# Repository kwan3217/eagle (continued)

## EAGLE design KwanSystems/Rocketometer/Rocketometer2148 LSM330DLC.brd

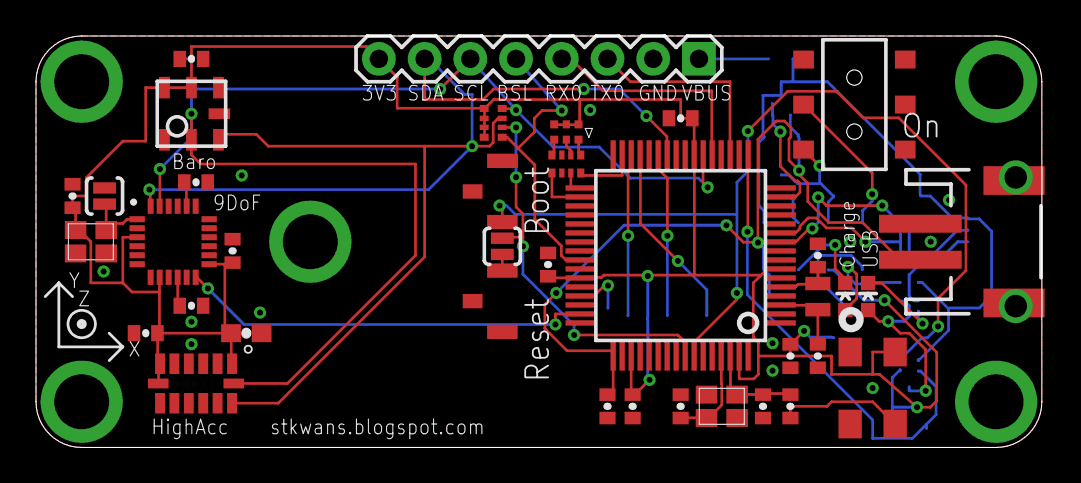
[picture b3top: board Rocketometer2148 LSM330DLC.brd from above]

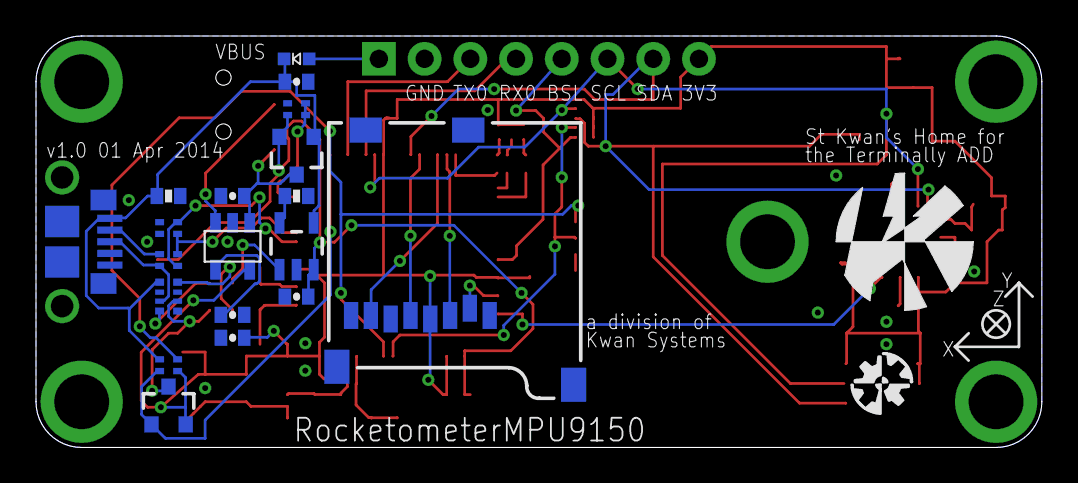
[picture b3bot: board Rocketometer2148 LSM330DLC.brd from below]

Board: 2 copper layers, 55.9 x 22.9 mm, 64 parts (21 on the bottom side), 46 nets.

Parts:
C023: 22pF; CKCM25
C101, C203, C443, C449, C601, C610, C613, C906: 100nF; 0402-CAP
C201, C301, C302: 4.7uF; 0402-CAP
C204, C423, C451, C463: 1uF; 0402-CAP
C403, C405: 22pF; 0402-CAP
C404: 100pF; 0402-CAP
C461, C462: 33pF; 0402-CAP
C620: 2.2nF; 0402-CAP
C901: 10uF; 0603-CAP
D050: BLUE; LED-0603
D301: YELLOW; LED-0603
D302: DCC; SOT-23-3
D401: SMLP36
D402: DIODE_SCHOTTKY; D0603
J001: USB_MICROB_JSTGCT; USB_MICROB_3075
J301: JST 2mm; JST-2-SMD
J401: M07; 1X08
J701: MICROSD-SOCKET; MICROSD-SOCKET-PP
JP1, JP2, JP3, JP4, JP5: STANDOFF
Q050: PMOS; SOT23-3
R011: 100k; 0402-RES
R015: 10k; CRA02
R023: 33; CRA02
R053, R402: 1.5k; CRA04
R301: 10k; 0402-RES
R302: 1M; CRA02
R401: 10k; CRA04
S201: AYZ0202
S457, S458: B3U-1100P
S457A, S457A1: SOLDERJUMPERNO; SJ_2S-NO
U101: BMP180
U201: 5319; SOT-23-5
U301: 73831; SOT23-5
U401: LPC2148; SQFP-S-10X10-64
U601: MPU9150; LLGA24
U902: ADXL375
U$4: AXES
U$5: KWAN_ACC
U$6: OSHW_ACC
Y401: 12MHz; CRYSTAL_SMD_2MM_2_5MM
Y402: 32kiHz; ABS06
Y403: 12MHz; CRYSTAL_SMD_5MM_3_2MM
Y601: 19.2MHz; CRYSTAL_SMD_2MM_2_5MM

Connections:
ACCINT: U401.47, U601.12
BATLVL: R302.3, R302.4, U401.15
BSL: J401.5, R401.1, U401.41
CONN_D+: J001.3, R023.2, R053.7
CONN_D-: J001.2, R023.1
CS0: J701.2, U401.45
EN: S201.5, U201.3
GND: C023.3, C023.4, C101.2, C201.2, C203.2, C204.2, C301.2, C302.2, C403.1, C405.2, C423.2, C443.2, C449.1, C451.2, C461.1, C462.1, C463.2, C601.1, C610.2, C613.1, C620.1, C901.2, C906.2, J001.5, J001.P$1, J001.P$2, J001.P$3, J001.P$4, J001.P$8, J001.P$10, J301.1, J401.2, J701.6, J701.CD2, J701.GND1, J701.GND3, JP1.P$1, JP2.P$1, JP3.P$1, JP4.P$1, JP5.P$1, R011.1, R053.1, R301.1, R302.1, S201.4, S457.P$2, S457.P$3, S457A1.2, S458.P$1, S458.P$3, U101.7, U201.2, U301.2, U401.6, U401.18, U401.25, U401.42, U401.50, U401.59, U601.9, U601.11, U601.15, U601.17, U601.18, U902.2, U902.4, U902.5, U902.12, Y401.2, Y401.4, Y403.2, Y601.1, Y601.2
MISO0: J701.7, U401.29
MOSI0: J701.3, U401.30
unnamed: C620.2, U601.20
unnamed: R301.2, U301.5
unnamed: D301.A, R053.4
unnamed: D301.C, U301.1
unnamed: C404.2, Y403.3
unnamed: D050.A, Q050.3, R053.2
unnamed: D050.C, R053.8
unnamed: D402.A, J401.1
unnamed: S457.P$1, S457A.2
unnamed: C610.1, U601.10
unnamed: C203.1, U201.4
OSC_9DOF: S457A1.1, U601.1, Y601.3
PWMB: R402.8, U401.31
PWMG: R402.5, U401.34
PWMR: R402.7, U401.33
QWMB: D401.1, R402.1
QWMG: D401.5, R402.4
QWMR: D401.3, R402.2
RESET: R401.2, S457A.1, U401.57
RTXC1: C403.2, U401.3, Y402.2
RTXC2: C405.1, U401.5, Y402.1
RX0: J401.4, U401.21
SCK0: J701.5, U401.27
SCL0: J401.6, R401.4, U101.5, U401.22, U601.23, U902.14
SDA0: J401.7, R401.3, U101.6, U401.26, U601.24, U902.13
TX0: J401.3, U401.19
USBD+: C023.2, R023.3, U401.10
USBD-: C023.1, R023.4, U401.11
USB_ON: R015.2, S458.P$2, U401.58
USB_SOFTCONNECT: Q050.1, R015.4, U401.17
VBUS: C302.1, D302.1, D402.C, J001.1, R011.2, R015.3, R053.5, U301.4
VCC: C101.1, C201.1, C423.1, C443.1, C451.1, C463.1, C601.2, C613.2, C901.1, C906.1, D401.2, D401.4, D401.6, J401.8, J701.4, Q050.2, R015.1, R401.5, R401.6, R401.7, R401.8, U101.2, U101.3, U201.5, U401.7, U401.23, U401.43, U401.51, U401.63, U601.3, U601.8, U601.13, U902.1, U902.6, U902.7, Y403.4, Y601.4
VIN: C204.1, D302.3, S201.6, U201.1
VLIPO: C301.1, C449.2, D302.2, J301.2, R302.2, U301.3, U401.49
XTAL1: C404.1, C462.2, U401.62, Y401.1
XTAL2: C461.2, U401.61, Y401.3

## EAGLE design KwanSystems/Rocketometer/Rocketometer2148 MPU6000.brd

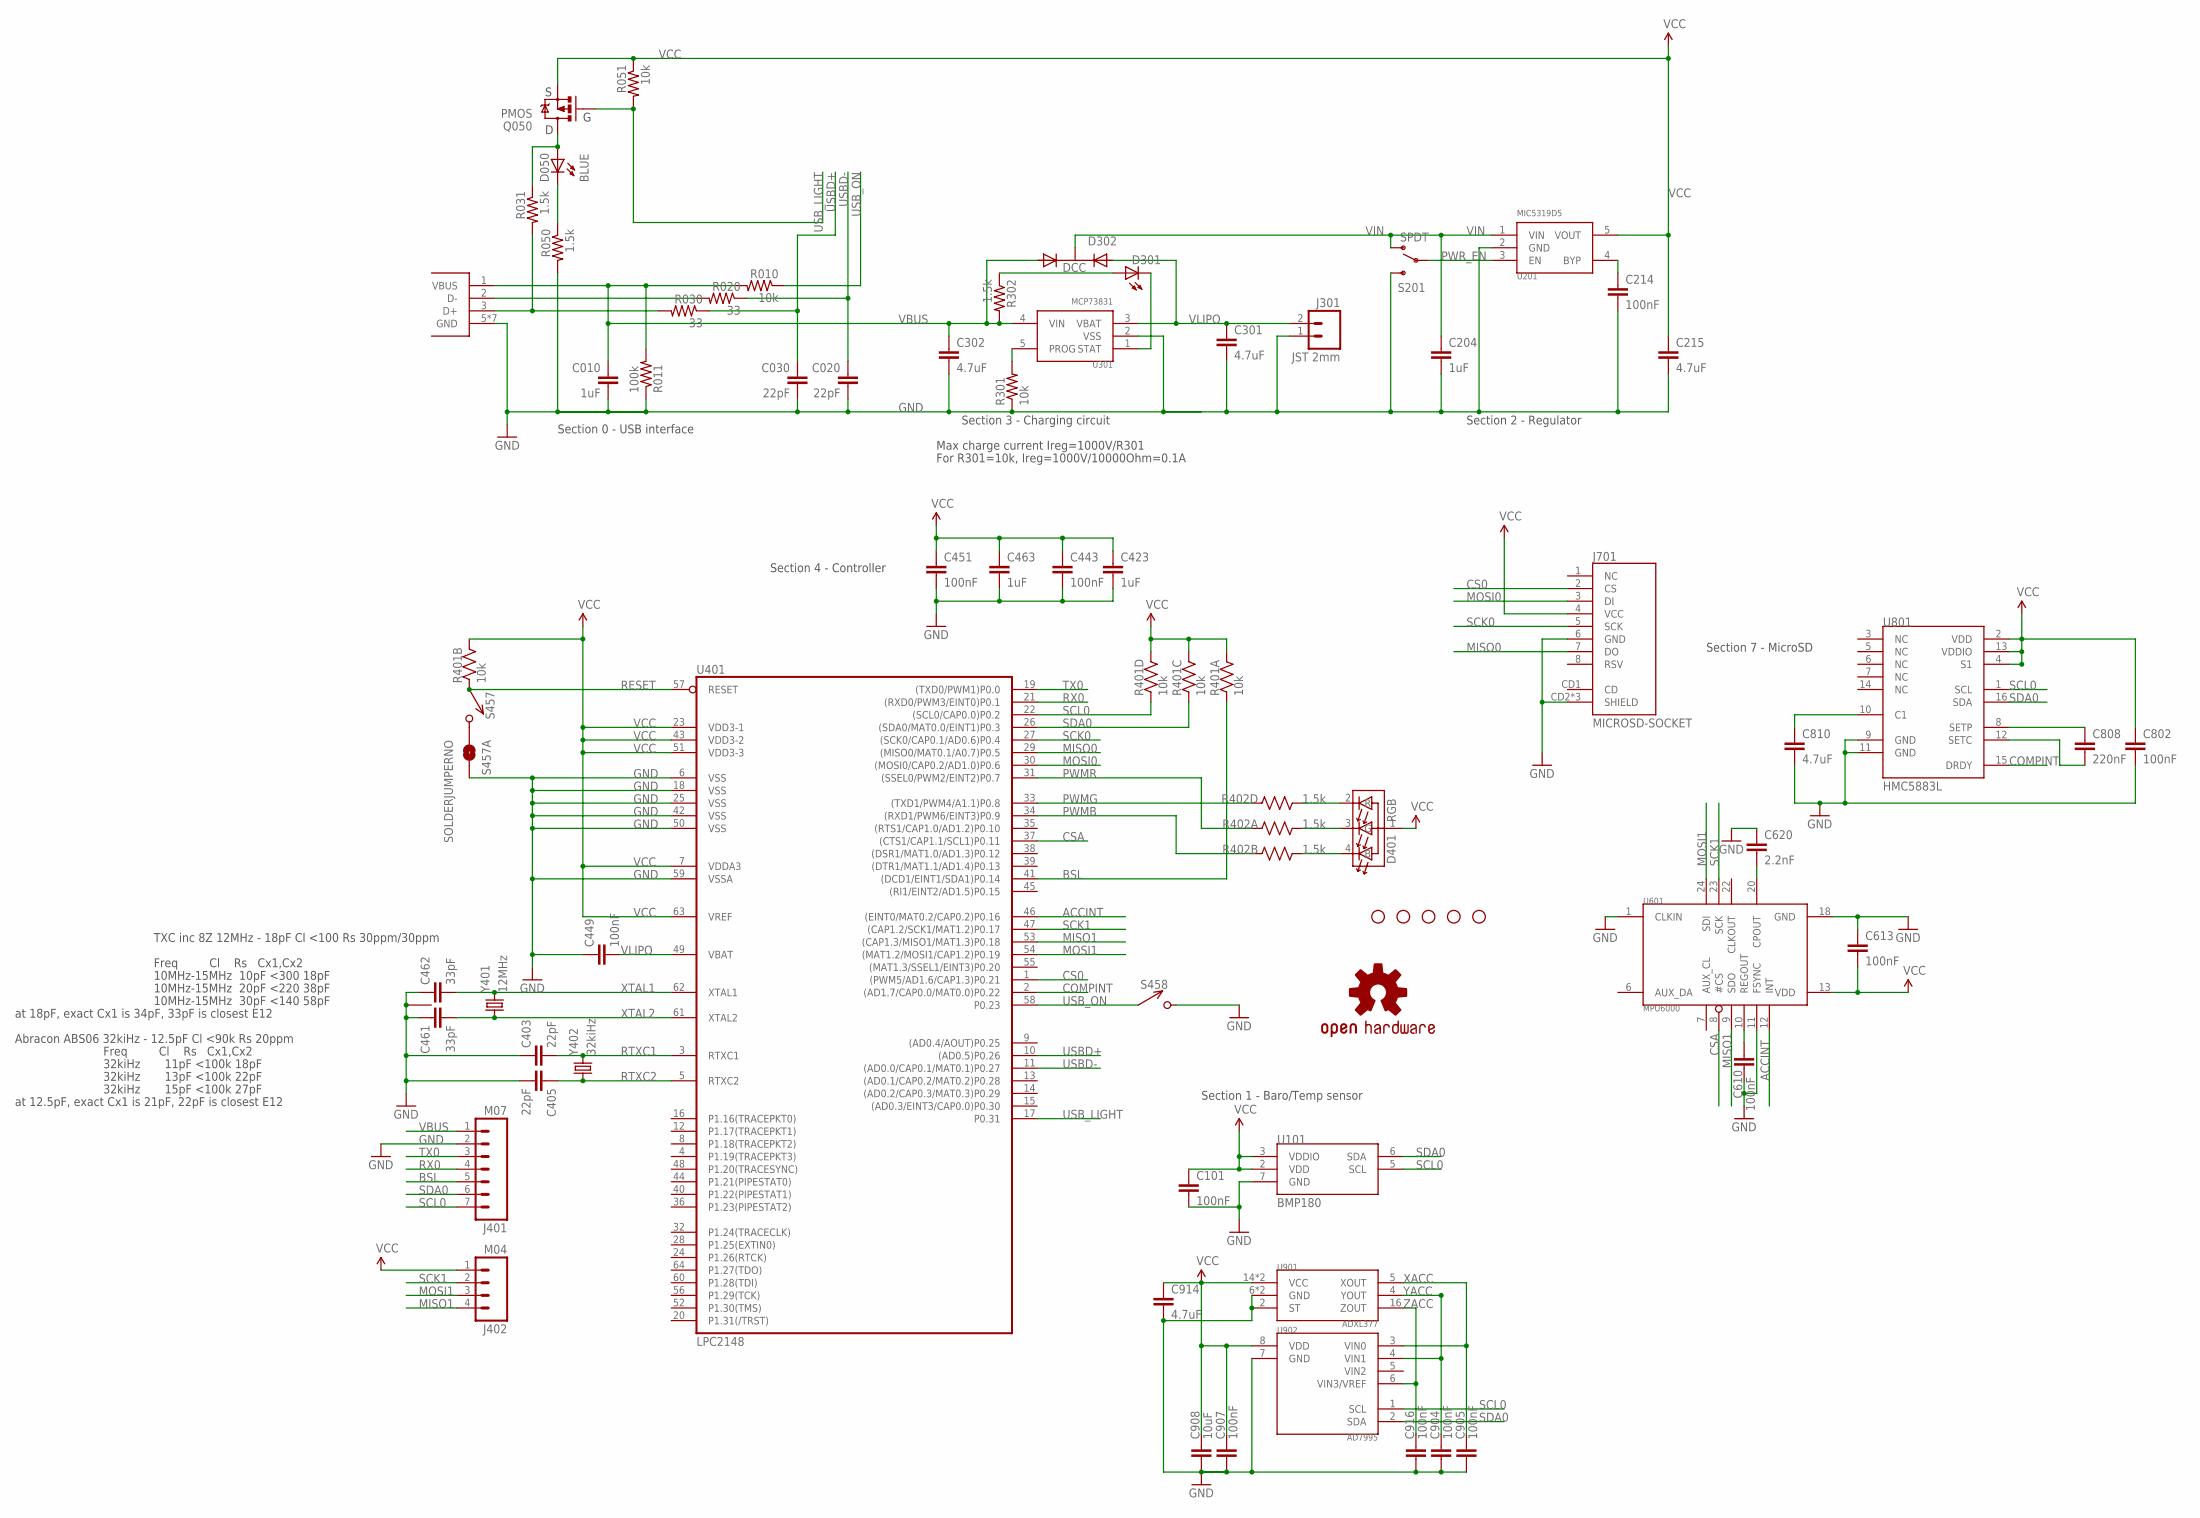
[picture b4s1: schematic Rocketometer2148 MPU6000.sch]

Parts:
C010, C204, C423, C463: 1uF; 0402-CAP; DIGIKEY 445-1415-1-ND
C020, C030, C403, C405: 22pF; 0402-CAP; DIGIKEY 445-5363-1-ND
C101, C214, C443, C449, C451, C610, C613, C802, C904, C905, C907, C916: 100nF; 0402-CAP; DIGIKEY 445-1268-1-ND
C215, C301, C302, C810, C914: 4.7uF; 0402-CAP; DIGIKEY 445-7395-1-ND
C461, C462: 33pF; 0402-CAP; DIGIKEY 445-1241-1-ND
C620: 2.2nF; 0402-CAP; DIGIKEY 445-1257-1-ND
C808: 220nF; 0402-CAP; DIGIKEY 445-4972-1-ND
C908: 10uF; 0603-CAP; DIGIKEY 445-7486-1-ND
D050: BLUE; LED-0603; DIGIKEY 350-2037-1-ND
D301: YELLOW; LED-0603; DIGIKEY 754-1124-1-ND
D302: DCC; SOT-23-3; DIGIKEY 568-6500-1-ND
D401: RGB; HSMF-C118; DIGIKEY 516-1778-1-ND
J001: USB_MICROB_JST; UB-MC5BR3-SD204-4S; DIGIKEY 455-2562-1-ND
J301: JST 2mm; JST-2-SMD; DIGIKEY 455-1749-1-ND
J401: M07; 1X07; DIGIKEY $NOPART
J402: M04; 1X04; DIGIKEY $NOPART
J701: MICROSD-SOCKET; MICROSD-SOCKET-PP; DIGIKEY 101-00581-59-1-ND
JP1, JP2, JP3, JP4, JP5: STAND-OFFTIGHT; STAND-OFF-TIGHT; DIGIKEY $NOPART
Q050: PMOS; SOT23-3; DIGIKEY NTR1P02T1GOSCT-ND
R010, R051, R301: 10k; 0402-RES; DIGIKEY P10.0KLCT-ND
R011: 100k; 0402-RES; DIGIKEY P100KLCT-ND
R020, R030: 33; 0402-RES; DIGIKEY P33.0LCT-ND
R031, R050, R302: 1.5k; 0402-RES; DIGIKEY P1.50KLCT-ND
R401: 10k; CRA04; DIGIKEY CRA4S810KCT-ND
R402: 1.5k; CRA04; DIGIKEY CRA4S81.5KCT-ND
S201: SPDT; AYZ0202; DIGIKEY 401-2013-1-ND
S457, S458: B3U-1000P; DIGIKEY SW1020CT-ND
S457A: SOLDERJUMPERNO; SJ_2S-NO; DIGIKEY $NOPART
U101: BMP180; DIGIKEY 828-1027-1-ND
U201: MIC5319D5; SOT-23-5; DIGIKEY 576-1910-1-ND
U301: MCP73831; SOT-23-5; DIGIKEY MCP73831T-2ACI/OTCT-ND
U401: LPC2148; SQFP-S-10X10-64; DIGIKEY 568-1765-ND
U601: MPU6000; MPU60X0; DIGIKEY $NOPART
U801: HMC5883L; 16LPCC; DIGIKEY 342-1082-1-ND
U901: ADXL377; DIGIKEY ADXL377BCPZ-RL7CT-ND
U902: AD7995; SOT-23-8; DIGIKEY AD7995YRJZ-1500RL7CT-ND
U$2: OSHW-LOGOS; OSHW-LOGO-S; DIGIKEY $NOPART
Y401: 12MHz; CRYSTAL_SMD_2MM_2_5MM; DIGIKEY 887-1487-1-ND
Y402: 32kiHz; ABS06; DIGIKEY 535-10104-1-ND

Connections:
ACCINT: U401.46 ((EINT0/MAT0.2/CAP0.2)P0.16), U601.12 (INT)
BSL: J401.5, R401.1, U401.41 ((DCD1/EINT1/SDA1)P0.14)
COMPINT: U401.2 ((AD1.7/CAP0.0/MAT0.0)P0.22), U801.15 (DRDY)
CONN_D+: J001.3 (D+), R030.2, R031.2
CONN_D-: J001.2 (D-), R020.2
CS0: J701.2 (CS), U401.1 ((PWM5/AD1.6/CAP1.3)P0.21)
CSA: U401.37 ((CTS1/CAP1.1/SCL1)P0.11), U601.8 (#CS)
GND: C010.2, C020.2, C030.2, C101.2, C204.2, C214.2, C215.2, C301.2, C302.2, C403.1, C405.2, C423.2, C443.2, C449.1, C451.2, C461.1, C462.1, C463.2, C610.2, C613.1, C620.1, C802.2, C810.2, C904.2, C905.2, C907.2, C908.2, C914.2, C916.2, J001.5 (GND), J001.P$6 (GND), J001.P$7 (GND), J001.P$8 (GND), J001.P$9 (GND), J001.P$10 (GND), J001.P$11 (GND), J301.1, J401.2, J701.6 (GND), J701.CD2 (SHIELD), J701.GND1 (SHIELD), J701.GND3 (SHIELD), R011.1, R050.2, R301.1, S201.3 (S), S457A.2, S458.P$2 (2), U101.7 (GND), U201.2 (GND), U301.2 (VSS), U401.6 (VSS), U401.18 (VSS), U401.25 (VSS), U401.42 (VSS), U401.50 (VSS), U401.59 (VSSA), U601.1 (CLKIN), U601.11 (FSYNC), U601.18 (GND), U801.9 (GND), U801.11 (GND), U901.2 (ST), U901.6 (GND), U901.7 (GND), U902.7 (GND), Y401.2 (1), Y401.4 (1)
MISO0: J701.7 (DO), U401.29 ((MISO0/MAT0.1/A0.7)P0.5)
MISO1: J402.4, U401.53 ((CAP1.3/MISO1/MAT1.3)P0.18), U601.9 (SDO)
MOSI0: J701.3 (DI), U401.30 ((MOSI0/CAP0.2/AD1.0)P0.6)
MOSI1: J402.3, U401.54 ((MAT1.2/MOSI1/CAP1.2)P0.19), U601.24 (SDI)
unnamed: C620.2, U601.20 (CPOUT)
unnamed: R301.2, U301.5 (PROG)
unnamed: D401.4 (B), R402.2 (1)
unnamed: D301.C, U301.1 (STAT)
unnamed: D301.A, R302.1
unnamed: D050.A, Q050.3 (D), R031.1
unnamed: D050.C, R050.1
unnamed: S457.P$2 (2), S457A.1
unnamed: D401.2 (R), R402.4 (1)
unnamed: D401.3 (G), R402.1
unnamed: C610.1, U601.10 (REGOUT)
unnamed: C808.1, U801.8 (SETP)
unnamed: C808.2, U801.12 (SETC)
unnamed: C810.1, U801.10 (C1)
unnamed: C214.1, U201.4 (BYP)
PWMB: R402.7 (2), U401.34 ((RXD1/PWM6/EINT3)P0.9)
PWMG: R402.5 (2), U401.33 ((TXD1/PWM4/A1.1)P0.8)
PWMR: R402.8 (2), U401.31 ((SSEL0/PWM2/EINT2)P0.7)
PWR_EN: S201.2, U201.3 (EN)
RESET: R401.2 (1), S457.P$1 (1), U401.57 (RESET)
RTXC1: C403.2, U401.3 (RTXC1), Y402.2
RTXC2: C405.1, U401.5 (RTXC2), Y402.1
RX0: J401.4, U401.21 ((RXD0/PWM3/EINT0)P0.1)
SCK0: J701.5 (SCK), U401.27 ((SCK0/CAP0.1/AD0.6)P0.4)
SCK1: J402.2, U401.47 ((CAP1.2/SCK1/MAT1.2)P0.17), U601.23 (SCK)
SCL0: J401.7, R401.4 (1), U101.5 (SCL), U401.22 ((SCL0/CAP0.0)P0.2), U801.1 (SCL), U902.1 (SCL)
SDA0: J401.6, R401.3 (1), U101.6 (SDA), U401.26 ((SDA0/MAT0.0/EINT1)P0.3), U801.16 (SDA), U902.2 (SDA)
TX0: J401.3, U401.19 ((TXD0/PWM1)P0.0)
USBD+: C030.1, R030.1, U401.10 ((AD0.5)P0.26)
USBD-: C020.1, R020.1, U401.11 ((AD0.0/CAP0.1/MAT0.1)P0.27)
USB_LIGHT: Q050.1 (G), R051.2, U401.17 (P0.31)
USB_ON: R010.1, S458.P$1 (1), U401.58 (P0.23)
VBUS: C010.1, C302.1, D302.1 (A1), J001.1 (VBUS), J401.1, R010.2, R011.2, R302.2, U301.4 (VIN)
VCC: C101.1, C215.1, C423.1, C443.1, C451.1, C463.1, C613.2, C802.1, C907.1, C908.1, C914.1, D401.1 (A), J402.1, J701.4 (VCC), Q050.2 (S), R051.1, R401.5 (2), R401.6 (2), R401.7 (2), R401.8 (2), U101.2 (VDD), U101.3 (VDDIO), U201.5 (VOUT), U401.7 (VDDA3), U401.23 (VDD3-1), U401.43 (VDD3-2), U401.51 (VDD3-3), U401.63 (VREF), U601.13 (VDD), U801.2 (VDD), U801.4 (S1), U801.13 (VDDIO), U901.14 (VCC), U901.15 (VCC), U902.8 (VDD)
VIN: C204.1, D302.3 (K), S201.1 (O), U201.1 (VIN)
VLIPO: C301.1, C449.2, D302.2 (A2), J301.2, U301.3 (VBAT), U401.49 (VBAT)
XACC: C905.1, U901.5 (XOUT), U902.3 (VIN0)
XTAL1: C462.2, U401.62 (XTAL1), Y401.3 (2)
XTAL2: C461.2, U401.61 (XTAL2), Y401.1
YACC: C904.1, U901.4 (YOUT), U902.4 (VIN1)
ZACC: C916.1, U901.16 (ZOUT), U902.6 (VIN3/VREF)

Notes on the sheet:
Section 2 - Regulator
Section 3 - Charging circuit
Section 0 - USB interface
Section 4 - Controller
Section 7 - MicroSD
Section 1 - Baro/Temp sensor
Max charge current Ireg=1000V/R301
For R301=10k, Ireg=1000V/10000Ohm=0.1A
Freq Cl Rs Cx1,Cx2
10MHz-15MHz 10pF <300 18pF
10MHz-15MHz 20pF <220 38pF
10MHz-15MHz 30pF <140 58pF
TXC inc 8Z 12MHz - 18pF Cl <100 Rs 30ppm/30ppm
at 18pF, exact Cx1 is 34pF, 33pF is closest E12
32kiHz 11pF <100k 18pF
32kiHz 13pF <100k 22pF
32kiHz 15pF <100k 27pF
Abracon ABS06 32kiHz - 12.5pF Cl <90k Rs 20ppm
at 12.5pF, exact Cx1 is 21pF, 22pF is closest E12

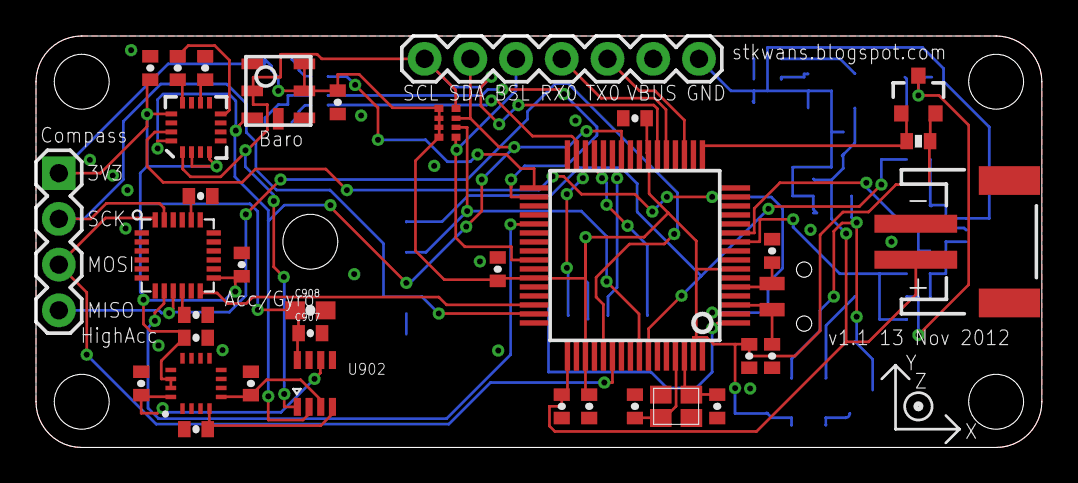
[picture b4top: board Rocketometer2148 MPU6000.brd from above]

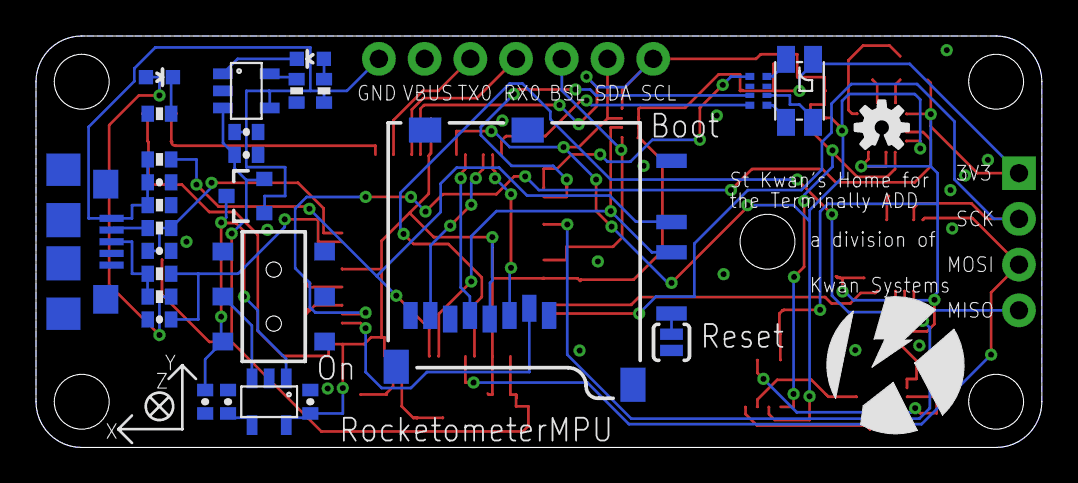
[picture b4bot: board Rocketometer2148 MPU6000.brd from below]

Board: 2 copper layers, 55.9 x 22.9 mm, 73 parts (31 on the bottom side), 53 nets.

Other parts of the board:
U$1: KWAN_CIRCLE
U$4: AXES
